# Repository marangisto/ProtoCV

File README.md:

# ProtoCV
Prototype Precision CV

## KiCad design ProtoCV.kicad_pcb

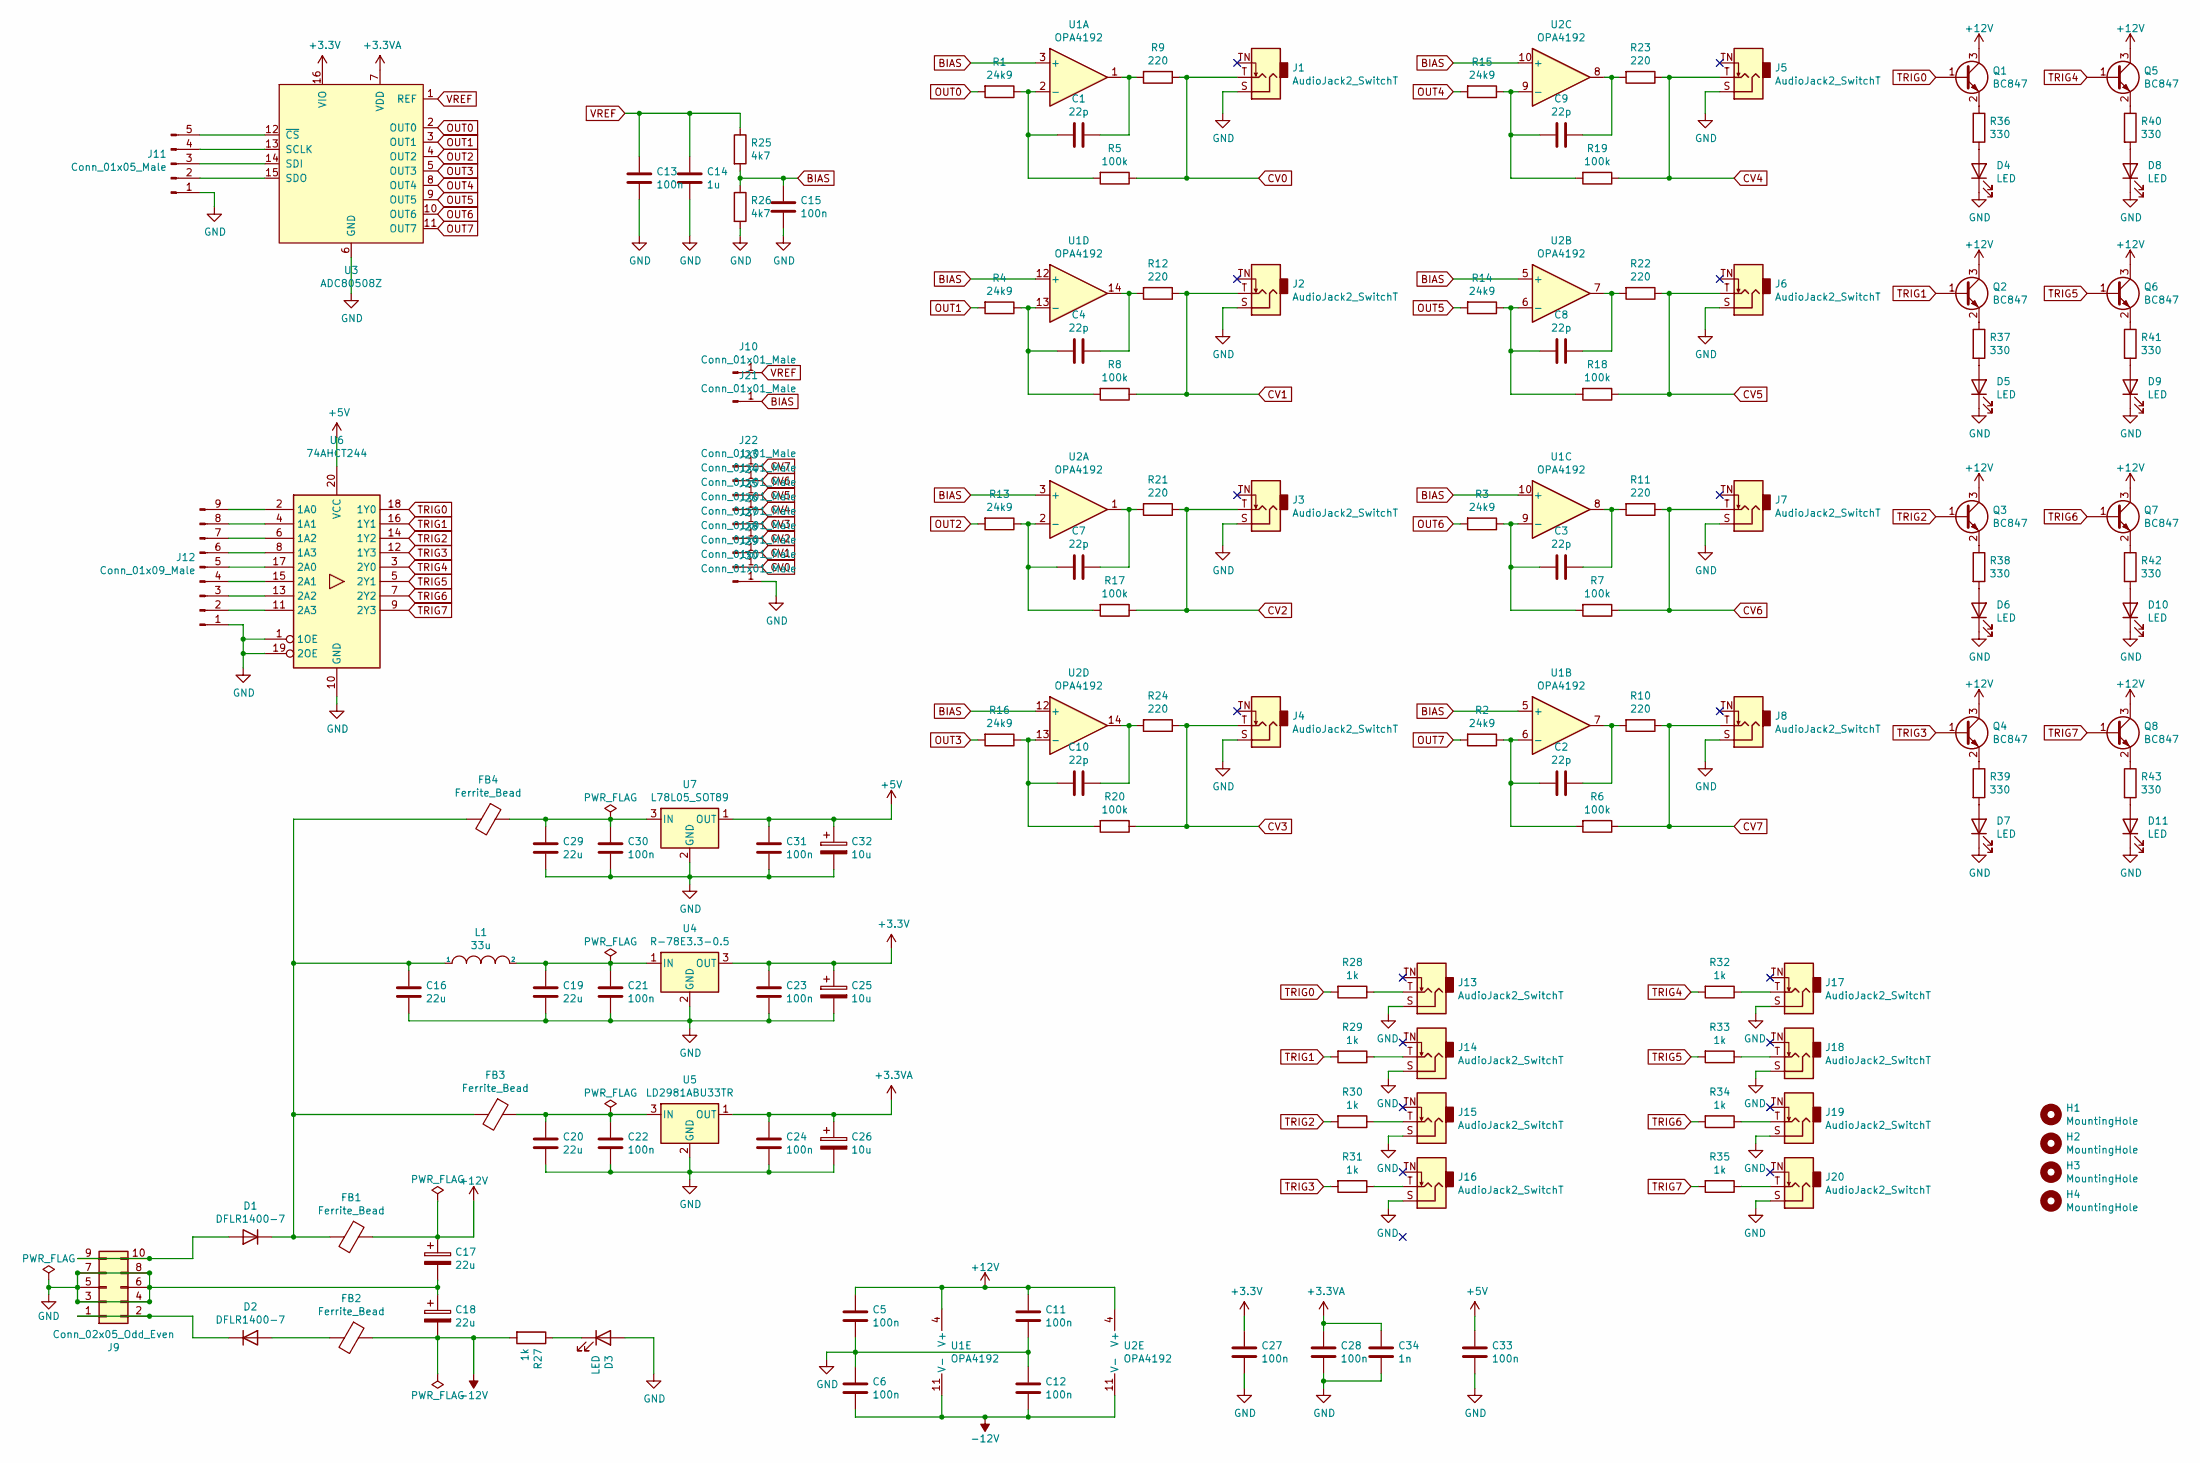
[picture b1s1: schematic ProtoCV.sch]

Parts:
C1, C2, C3, C4, C7, C8, C9, C10: 22p; C_0603_1608Metric
C5, C6, C11, C12, C13, C15, C21, C22, C23, C24, C27, C28, C30, C31, C33: 100n; C_0603_1608Metric
C14: 1u; C_0603_1608Metric
C16, C19, C20, C29: 22u; C_1206_3216Metric
C17, C18: 22u; CP_Elec_5x5.4
C25, C26, C32: 10u; CP_Elec_4x5.8
C34: 1n; C_0603_1608Metric
D1, D2: DFLR1400-7; D_PowerDI-123
D3, D4, D5, D6, D7, D8, D9, D10, D11: LED; LED_0603_1608Metric_Castellated
FB1, FB2, FB3, FB4: Ferrite_Bead; L_0603_1608Metric
H1, H2, H3, H4: MountingHole; MountingHole_3.2mm_M3_Pad_Via
J1, J2, J3, J4, J5, J6, J7, J8, J13, J14, J15, J16, J17, J18, J19, J20: AudioJack2_SwitchT; PJ398SM
J9: Conn_02x05_Odd_Even; PinHeader_2x05_P2.54mm_Vertical
J10, J21, J22, J23, J24, J25, J26, J27, J28, J29, J30: Conn_01x01_Male; PinHeader_1x01_P2.54mm_Vertical
J11: Conn_01x05_Male; PinHeader_1x05_P2.54mm_Vertical
J12: Conn_01x09_Male; PinHeader_1x09_P2.54mm_Vertical
L1: 33u; L_0805_2012Metric
Q1, Q2, Q3, Q4, Q5, Q6, Q7, Q8: BC847; SOT-23
R1, R2, R3, R4, R13, R14, R15, R16: 24k9; R_0603_1608Metric
R5, R6, R7, R8, R17, R18, R19, R20: 100k; R_0603_1608Metric
R9, R10, R11, R12, R21, R22, R23, R24: 220; R_1206_3216Metric
R25, R26: 4k7; R_0603_1608Metric
R27, R28, R29, R30, R31, R32, R33, R34, R35: 1k; R_0603_1608Metric
R36, R37, R38, R39, R40, R41, R42, R43: 330; R_0603_1608Metric
U1, U2: OPA4192; TSSOP-14_4.4x5mm_P0.65mm
U3: ADC80508Z; QFN-16-1EP_3x3mm_P0.5mm_EP1.45x1.45mm_ThermalVias
U4: R-78E3.3-0.5; Converter_DCDC_RECOM_R-78E-0.5_THT
U5: LD2981ABU33TR; SOT-89-3
U6: 74AHCT244; TSSOP-20_4.4x6.5mm_P0.65mm
U7: L78L05_SOT89; SOT-89-3

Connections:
+3.3VA: C24.1, C26.1, C28.1, C34.1, U3.7 (VDD), U5.1 (OUT)
+3V3: C23.1, C25.1, C27.1, U3.16 (VIO), U4.3 (OUT)
+5V: C31.1, C32.1, C33.1, U6.20 (VCC), U7.1 (OUT)
+12V: C5.1, C11.1, C17.1, FB1.1, Q1.3 (C), Q2.3 (C), Q3.3 (C), Q4.3 (C), Q5.3 (C), Q6.3 (C), Q7.3 (C), Q8.3 (C), U1.4 (V+), U2.4 (V+)
-12V: C6.2, C12.2, C18.2, FB2.1, R27.2, U1.11 (V-), U2.11 (V-)
BIAS: C15.1, J21.1, R25.2, R26.1, U1.3 (+), U1.5 (+), U1.10 (+), U1.12 (+), U2.3 (+), U2.5 (+), U2.10 (+), U2.12 (+)
CV0: J1.T, J29.1, R5.1, R9.1
CV1: J2.T, J28.1, R8.1, R12.1
CV2: J3.T, J27.1, R17.1, R21.1
CV3: J4.T, J26.1, R20.1, R24.1
CV4: J5.T, J25.1, R19.1, R23.1
CV5: J6.T, J24.1, R18.1, R22.1
CV6: J7.T, J23.1, R7.1, R11.1
CV7: J8.T, J22.1, R6.1, R10.1
GND: C5.2, C6.1, C11.2, C12.1, C13.2, C14.2, C15.2, C16.2, C17.2, C18.1, C19.2, C20.2, C21.2, C22.2, C23.2, C24.2, C25.2, C26.2, C27.2, C28.2, C29.2, C30.2, C31.2, C32.2, C33.2, C34.2, D3.2 (A), D4.1 (K), D5.1 (K), D6.1 (K), D7.1 (K), D8.1 (K), D9.1 (K), D10.1 (K), D11.1 (K), J1.S, J2.S, J3.S, J4.S, J5.S, J6.S, J7.S, J8.S, J9.3, J9.4, J9.5, J9.6, J9.7, J9.8, J11.1, J12.1, J13.S, J14.S, J15.S, J16.S, J17.S, J18.S, J19.S, J20.S, J30.1, R26.2, U3.6 (GND), U4.2 (GND), U5.2 (GND), U6.1 (1OE), U6.10 (GND), U6.19 (2OE), U7.2 (GND)
unnamed: C1.1, R9.2, U1.1
unnamed: C1.2, R1.1, R5.2, U1.2 (-)
unnamed: C2.1, R10.2, U1.7
unnamed: C2.2, R2.1, R6.2, U1.6 (-)
unnamed: C3.1, R11.2, U1.8
unnamed: C3.2, R3.1, R7.2, U1.9 (-)
unnamed: C4.1, R12.2, U1.14
unnamed: C4.2, R4.1, R8.2, U1.13 (-)
unnamed: C7.1, R21.2, U2.1
unnamed: C7.2, R13.1, R17.2, U2.2 (-)
unnamed: C8.1, R22.2, U2.7
unnamed: C8.2, R14.1, R18.2, U2.6 (-)
unnamed: C9.1, R23.2, U2.8
unnamed: C9.2, R15.1, R19.2, U2.9 (-)
unnamed: C10.1, R24.2, U2.14
unnamed: C10.2, R16.1, R20.2, U2.13 (-)
unnamed: C16.1, D1.1 (K), FB1.2, FB3.2, FB4.2, L1.1
unnamed: C19.1, C21.1, L1.2, U4.1 (IN)
unnamed: C20.1, C22.1, FB3.1, U5.3 (IN)
unnamed: C29.1, C30.1, FB4.1, U7.3 (IN)
unnamed: D1.2 (A), J9.9, J9.10
unnamed: D2.1 (K), J9.1, J9.2
unnamed: D2.2 (A), FB2.2
unnamed: D3.1 (K), R27.1
unnamed: D4.2 (A), R36.2
unnamed: D5.2 (A), R37.2
unnamed: D6.2 (A), R38.2
unnamed: D7.2 (A), R39.2
unnamed: D8.2 (A), R40.2
unnamed: D9.2 (A), R41.2
unnamed: D10.2 (A), R42.2
unnamed: D11.2 (A), R43.2
unnamed: J11.2, U3.15 (SDO)
unnamed: J11.3, U3.14 (SDI)
unnamed: J11.4, U3.13 (SCLK)
unnamed: J11.5, U3.12 (~CS~)
unnamed: J12.2, U6.11 (2A3)
unnamed: J12.3, U6.13 (2A2)
unnamed: J12.4, U6.15 (2A1)
unnamed: J12.5, U6.17 (2A0)
unnamed: J12.6, U6.8 (1A3)
unnamed: J12.7, U6.6 (1A2)
unnamed: J12.8, U6.4 (1A1)
unnamed: J12.9, U6.2 (1A0)
unnamed: J13.T, R28.1
unnamed: J14.T, R29.1
unnamed: J15.T, R30.1
unnamed: J16.T, R31.1
unnamed: J17.T, R32.1
unnamed: J18.T, R33.1
unnamed: J19.T, R34.1
unnamed: J20.T, R35.1
unnamed: Q1.2 (E), R36.1
unnamed: Q2.2 (E), R37.1
unnamed: Q3.2 (E), R38.1
unnamed: Q4.2 (E), R39.1
unnamed: Q5.2 (E), R40.1
unnamed: Q6.2 (E), R41.1
unnamed: Q7.2 (E), R42.1
unnamed: Q8.2 (E), R43.1
OUT0: R1.2, U3.2 (OUT0)
OUT1: R4.2, U3.3 (OUT1)
OUT2: R13.2, U3.4 (OUT2)
OUT3: R16.2, U3.5 (OUT3)
OUT4: R15.2, U3.8 (OUT4)
OUT5: R14.2, U3.9 (OUT5)
OUT6: R3.2, U3.10 (OUT6)
OUT7: R2.2, U3.11 (OUT7)
TRIG0: Q1.1 (B), R28.2, U6.18 (1Y0)
TRIG1: Q2.1 (B), R29.2, U6.16 (1Y1)
TRIG2: Q3.1 (B), R30.2, U6.14 (1Y2)
TRIG3: Q4.1 (B), R31.2, U6.12 (1Y3)
TRIG4: Q5.1 (B), R32.2, U6.3 (2Y0)
TRIG5: Q6.1 (B), R33.2, U6.5 (2Y1)
TRIG6: Q7.1 (B), R34.2, U6.7 (2Y2)
TRIG7: Q8.1 (B), R35.2, U6.9 (2Y3)
VREF: C13.1, C14.1, J10.1, R25.1, U3.1 (REF)

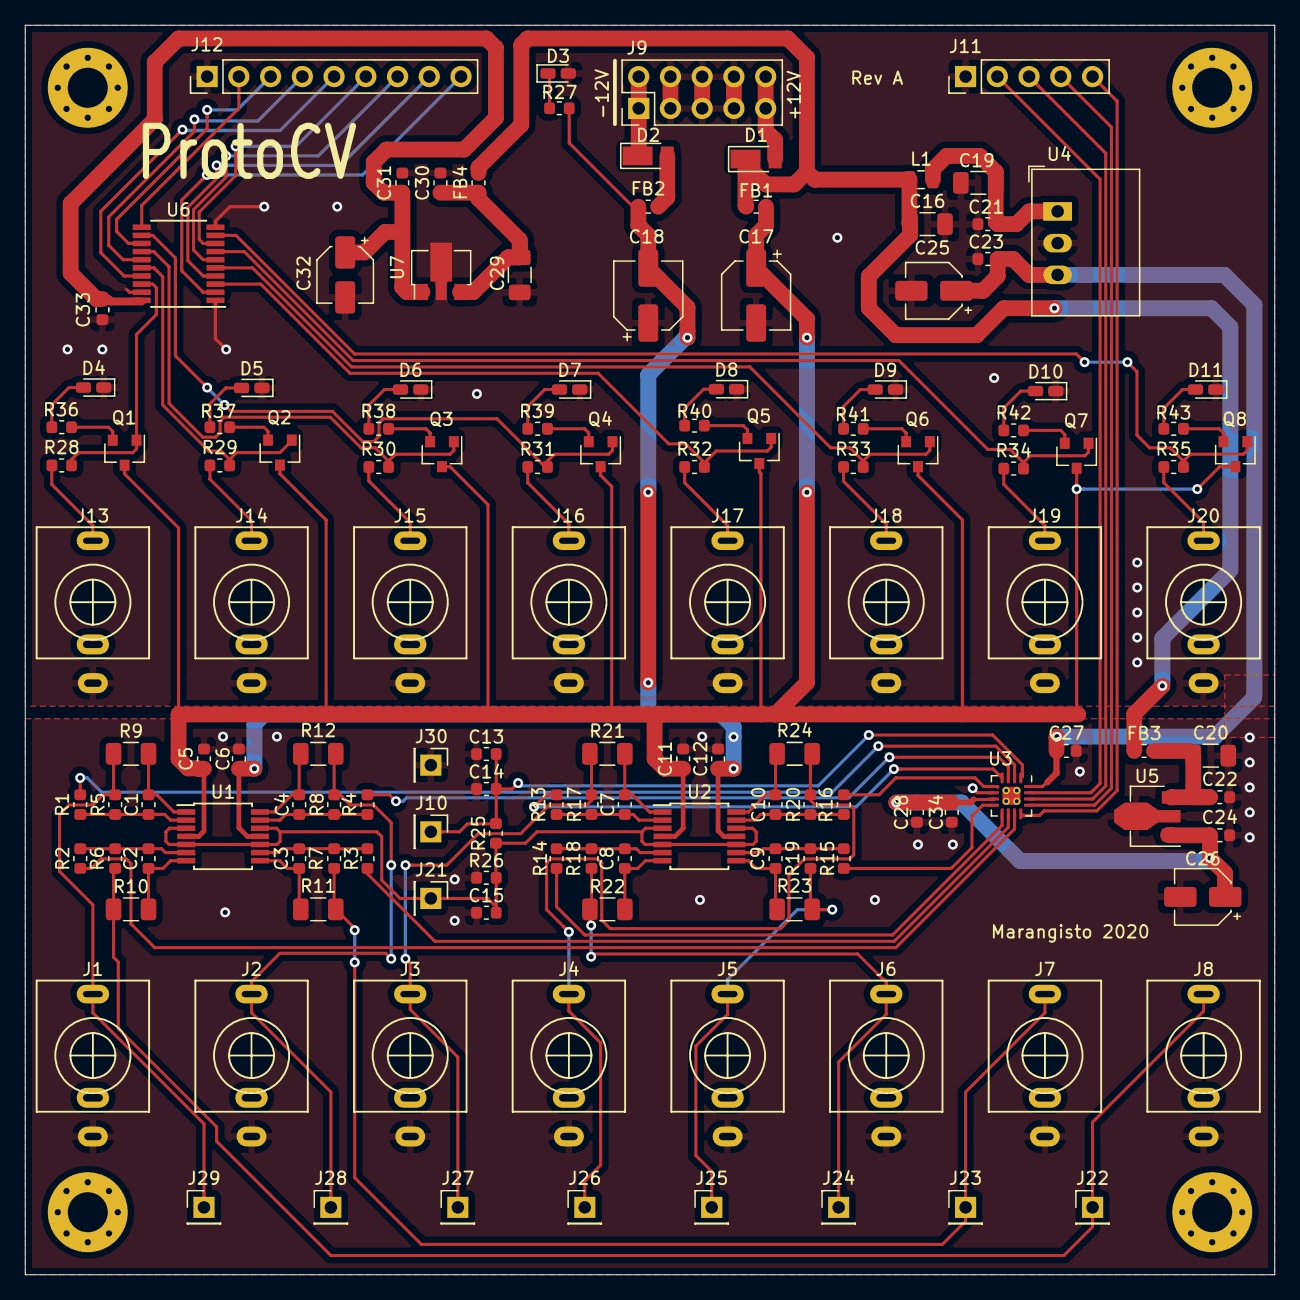
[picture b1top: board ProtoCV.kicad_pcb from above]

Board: 2 copper layers, 100.0 x 100.0 mm, 142 parts (0 on the bottom side), 92 nets.

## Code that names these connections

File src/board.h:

#pragma once

#include <usart.h>
#include "dac80508.h"

using led = output_t<PB8>;
using trig0 = output_t<PA10>;
using trig1 = output_t<PA9>;
using trig2 = output_t<PA12>;
using trig3 = output_t<PB0>;
using trig4 = output_t<PB7>;
using trig5 = output_t<PB5>;
using trig6 = output_t<PB6>;
using trig7 = output_t<PA8>;
using serial = usart_t<2, PA2, PA3>;

using dac = dac80508_t<spi_t<1, PB3, PA7, PA6>, PA0>;

template<> void handler<interrupt::USART2>()
{
    led::toggle();
    serial::isr();
}

struct calib_t
{
    float v0, v1;
};

static calib_t calib[] =
    { { 3.75656, -1.25902 }
    , { 3.75688, -1.25824 }
    , { 3.75614, -1.25877 }
    , { 3.75537, -1.26138 }
    , { 3.75619, -1.25913 }
    , { 3.75568, -1.26095 }
    , { 3.75546, -1.26048 }
    , { 3.75616, -1.25911 }
    };

template<int CH>
static uint16_t voltage(float x)
{
    const float v0 = calib[CH].v0;
    const float v1 = calib[CH].v1;
    const uint32_t k = 0xffff;
    const uint32_t k2 = k >> 1;
    const uint32_t k4 = k >> 2;

    float y = (x - v0) / (v1 - v0);

    return static_cast<uint16_t>(y * k2 + k4);
}

static void setup()
{
    led::setup();
    trig0::setup();
    trig1::setup();
    trig2::setup();
    trig3::setup();
    trig4::setup();
    trig5::setup();
    trig6::setup();
    trig7::setup();

    dac::setup();

    serial::setup<115200>();
    interrupt::set<interrupt::USART2>();
    interrupt::enable();

    dac::write(dac::CONFIG, 0x0000);
    dac::write(dac::GAIN, 0x01ff);

    dac::write(dac::DAC0, voltage<0>(0));
    dac::write(dac::DAC1, voltage<1>(0));
    dac::write(dac::DAC2, voltage<2>(0));
    dac::write(dac::DAC3, voltage<3>(0));
    dac::write(dac::DAC4, voltage<4>(0));
    dac::write(dac::DAC5, voltage<5>(0));
    dac::write(dac::DAC6, voltage<6>(0));
    dac::write(dac::DAC7, voltage<7>(0));

    /*
    // calibration settings
  
    static const uint32_t x0 = 0xffff >> 2;
    static const uint32_t x1 = (0xffff >> 1) + x0;


    dac::write(dac::DAC0, x1);
    dac::write(dac::DAC1, x1);
    dac::write(dac::DAC2, x1);
    dac::write(dac::DAC3, x1);
    dac::write(dac::DAC4, x1);
    dac::write(dac::DAC5, x1);
    dac::write(dac::DAC6, x1);
    dac::write(dac::DAC7, x1);
    */
}

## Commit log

2020-07-12 Created DAC symbol.
2020-07-12 Draft schematic.
2020-07-12 Added triggers.
2020-07-12 Cleaned up ERC.
2020-07-12 Added leds and drivers.
2020-07-12 Assigned footprints.
2020-07-12 Starting placement.
2020-07-12 Completed placement.
2020-07-13 Improved placement with separate analogue section.
2020-07-13 Added keep-outs under jacks.
2020-07-13 Minor layout adjustments.
2020-07-13 Power routing and split ground pour.
2020-07-13 Lots of manual routing.
2020-07-13 Front side pours.
2020-07-14 Near complete manual routing.
2020-07-14 Completed routing and DRC.
2020-07-14 Front silk-screen.
2020-07-14 Branding.
2020-07-14 Added artwork.
2020-07-14 Generated gerbers.
2020-07-14 Added some images.
2020-07-27 Added initial firmware.
2020-07-28 First working DAC driver code.
2020-07-28 Enabled basic calibration (good to a fifth milli-volt).
2020-07-28 Refactored board setup in separate file.
2020-07-28 Basic MIDI emulation.
2020-07-29 Corrected led resistor values.
2020-07-30 Generated schematic PDF.
2020-12-03 Corrected footprint for 5V regulator.
2020-12-03 Regenerated Gerbers.
